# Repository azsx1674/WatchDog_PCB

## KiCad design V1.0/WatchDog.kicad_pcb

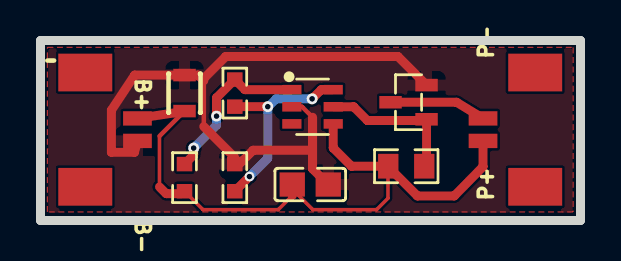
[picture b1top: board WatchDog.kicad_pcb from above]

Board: 2 copper layers, 30.0 x 10.0 mm, 10 parts (0 on the bottom side), 6 nets.

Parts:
C1: CAP-SMD_L2.0-W1.25
C2: C0805
Q1: SOT-23-3_L2.9-W1.3-P1.90-LS2.4-BR
R1, R2, R4: R0603
R3: R0805
U1: SOT-23-6_L2.9-W1.6-P0.95-LS2.8-BL
U2, U3: CONN-SMD_532610271

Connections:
$1N10: C1.2, C2.1, R1.1, R3.2, U1.4, U2.1, U3.1
$1N13: R1.2, R2.1, U1.1
$1N14: R2.2, R4.2, U1.6
$1N17: Q1.1, R3.1, U1.5
$1N19: Q1.3, U3.2
GND: C1.1, C2.2, Q1.2, R4.1, U1.2, U2.2

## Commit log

2026-05-01 docs: 新增 README.md 檔案
2026-05-01 chore(license): 新增 LICENSE 檔案
2026-05-09 chore: 新增 .gitignore 檔案
2026-05-09 feat(easyeda): 上傳 EasyEDA 專案檔
2026-05-09 feat(release): 上傳 BOM、Gerber、Pick and Place 檔案
2026-05-09 feat: 新增 WatchDog PCB、原理圖及 Kicad 專案檔案
2026-05-09 feat: 更新 WatchDog PCB、原理圖及 Kicad 專案檔案
